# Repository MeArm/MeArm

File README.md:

MeArm - Pocket Sized Robot Arm 
===========================

The MeArm is a small robot arm, designed make robotics and coding available at low cost. The project has been hugely successful in its objectives, due to the massive number of clones that have been made and sold across the world. There isn't an online market place where you can't buy a copy of this project. We continue to support the product through income made from the sale of high quality robot kits, manufactured and shipped from the UK.

[MeArm Website](https://www.mearm.com/) Where kits are available to purchase.

[MeArm GitHub](https://github.com/MeArm) Code and resources.

[phenoptix Thingiverse](https://www.thingiverse.com/phenoptix/designs) Physical designs and dxf files, alternative hosting, and other designed products.

Controllers and firmware for the MeArm are available for many different platforms, and can all be found in our [company github](https://github.com/MeArm).

## Available Controllers

Arduino
  - [Library with Inverse Kinematics](https://github.com/MeArm/MeArm-Arduino)
  - pcb V1.0 - AKA Brains Board using Pro Mini Clone
  - pcb V2.0 - AKA MeArm Wifi using ESP8266

Raspberry Pi
  - [node.js control](https://github.com/MeArm/mearm-js)
  - pcb V1.0 MeArm Pi

micro:bit 
  - [pxt adds blocks to makecode](https://github.com/MeArm/pxt-microbit-mearm)
  - [makecode hosted on microbit.org](https://makecode.microbit.org/22476-86653-83739-82174)
  - pcb all versions AKA MeArm micro:bit 

BeagleBoneBlack -[ Software hosted by Bob Stone](https://github.com/RorschachUK/meArmBBB)

Espruino - [JS Hardware with MeArm Examples](https://www.espruino.com/MeArm)

SparkCore - [Software with features such as S-Curve movements
](https://github.com/Hack-a-Day/Spark-MeArm)

Repository Contents
-------------------
This repository contains the design and cutting files for the MeArm. The MeArm is an Open Source 4DOF robot arm. It is intended to be a low cost and accessible robotics project for STEAM education.

Laser cut (3mm) dxf files and Assembly instruction pdf files are sorted into folders based on versions.

Files are collected from the various sources listed above.

## Watch the Build Video on YouTube

Version History
---------------

Available in this repository

* V3.0 Revised with no elastic bands, still requires a PCB. Build time around 40 minutes.
* V2.0 Designed for MeArm Pi Kickstarter, incorporates a PCB in the base. Requires elastic bands or nitrile O rings. Build time 30 minutes.
* V1.0 First finished version. No PCB required. Build time around 2 hours.

All hosted on Thingiverse .

* V1.0 ([First Finished Version](http://www.thingiverse.com/thing:993759))
* V0.4 ([Considered the Beta Arm](http://www.thingiverse.com/thing:360108))
* V0.3 ([Considered the Alpha Arm](http://www.thingiverse.com/thing:298820))
* V0.2 ([Heavy Weight Revision](http://www.thingiverse.com/thing:293707))
* V0.1 ([Proof of Concept](http://www.thingiverse.com/thing:257990))

License Information
-------------------
The hardware is released under [Creative Commons Share-alike 3.0](http://creativecommons.org/licenses/by-sa/3.0/).  
All other code is open source so please feel free to do anything you want with it; you buy me a beer if you use this and we meet someday ([Beerware license](http://en.wikipedia.org/wiki/Beerware)).
Also this boiler plate is yoinked from Sparkfun with thanks. Images are CC-SA-NC soz, have the files and design but take your own pics ;)

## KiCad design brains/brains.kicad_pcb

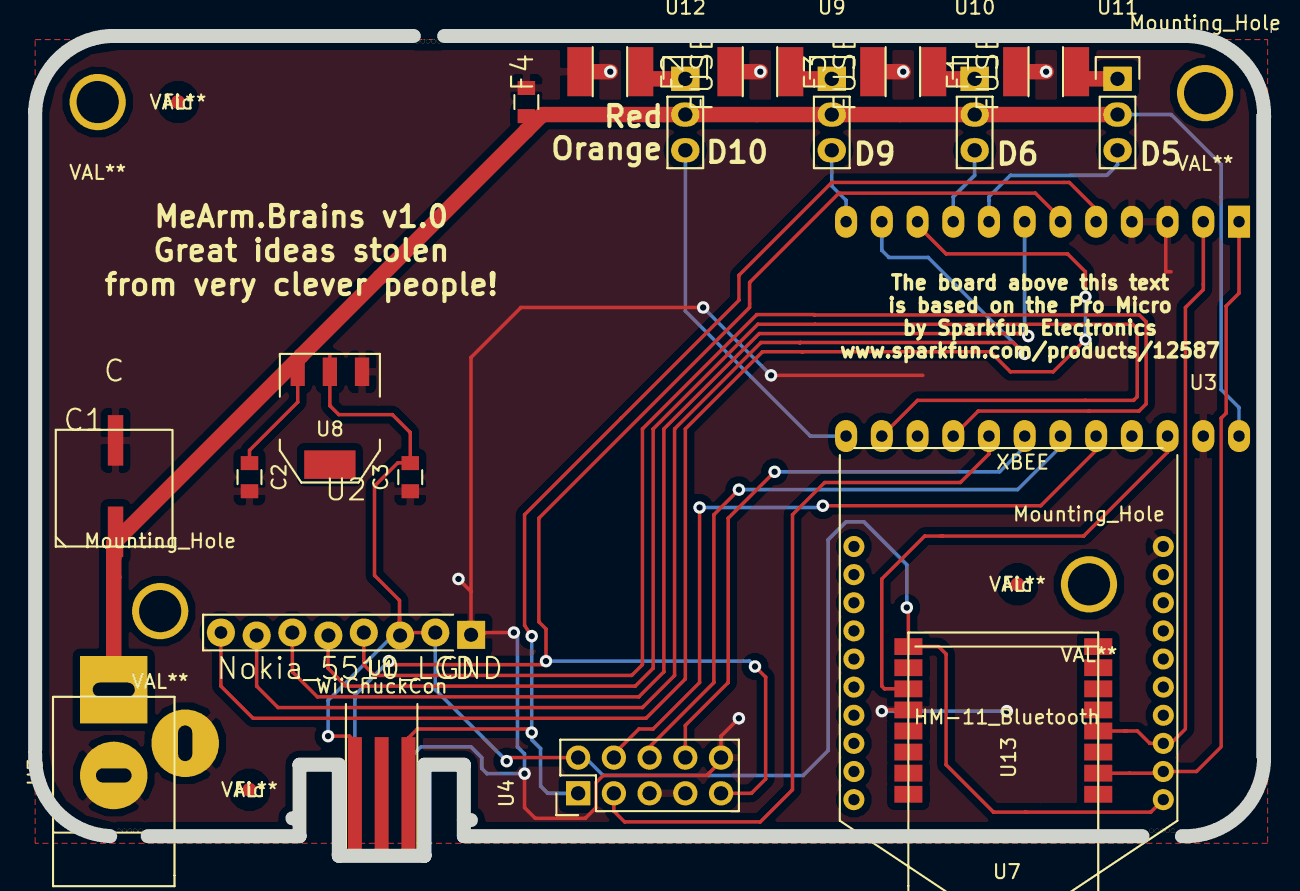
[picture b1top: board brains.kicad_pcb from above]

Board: 4 copper layers, 87.4 x 58.4 mm, 26 parts (0 on the bottom side), 25 nets.

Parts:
C1: C; EEE1CA471UP_Capacitor
C2: 10uF; C_0805
C3: 22uF; C_0805
C4: C; C_0805
F1, F2, F3, F4: FUSE; Surface_Mount_1812_Polyfuse
Fid: VAL**; Fid
Fid#2, Fid#3: VAL**; Fid
Mounting_Hole: VAL**; Mounting_Hole
Mounting_Hole#2, Mounting_Hole#3: VAL**; Mounting_Hole
U1: WiiChuckCon; WiiChuck
U2: Nokia_5510_LCD; Nokia5510LCD
U3: promicro; DIP-24__600_ELL
U4: JoyConnectISP; Pin_Header_Straight_2x05
U5: JACK_2MM1; JACK_ALIM
U7: HM-11_Bluetooth; HM-11_BT
U8: AP1117_V_REG; SOT-223
U9, U10, U11, U12: Pin_Header_Straight_1x03
U13: XBEE

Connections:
+3V3: C3.2, U1.1, U2.6, U2.7, U4.2, U7.9, U8.2, U13.1
+6V: C1.1, C2.1, C4.1, U3.24, U5.1, U8.3, U9.2, U10.2, U11.2, U12.2
A0: U3.17, U4.3
A1: U3.18, U4.8
A2: U3.19, U4.6
A3: U3.20, U4.4
BT_RX: U3.2, U7.4, U13.3
BT_TX: U3.1, U7.2, U13.2
CLAW: U3.13, U12.3
GND: C1.2, C2.2, C3.1, C4.2, F1.2, F2.2, F3.2, F4.2, U1.6, U2.8, U3.3, U3.4, U3.23, U4.5, U4.7, U4.10, U5.2, U5.3, U7.12, U8.1, U13.10
I2C_SCLK: U1.4, U3.6, U4.9
I2C_SDA: U1.3, U3.5, U4.1
LCD_CE: U2.2, U3.11
LCD_DC: U2.3, U3.7
LCD_RST: U2.1, U3.10
LEFT: U3.9, U10.3
MOSI_D16: U2.4, U3.14
unnamed: F1.1, U9.1
unnamed: F2.1, U10.1
unnamed: F3.1, U11.1
unnamed: F4.1, U12.1
RIGHT: U3.8, U11.3
RST: U3.22, U7.11
SCLK_D15: U2.5, U3.16
WAIST: U3.12, U9.3

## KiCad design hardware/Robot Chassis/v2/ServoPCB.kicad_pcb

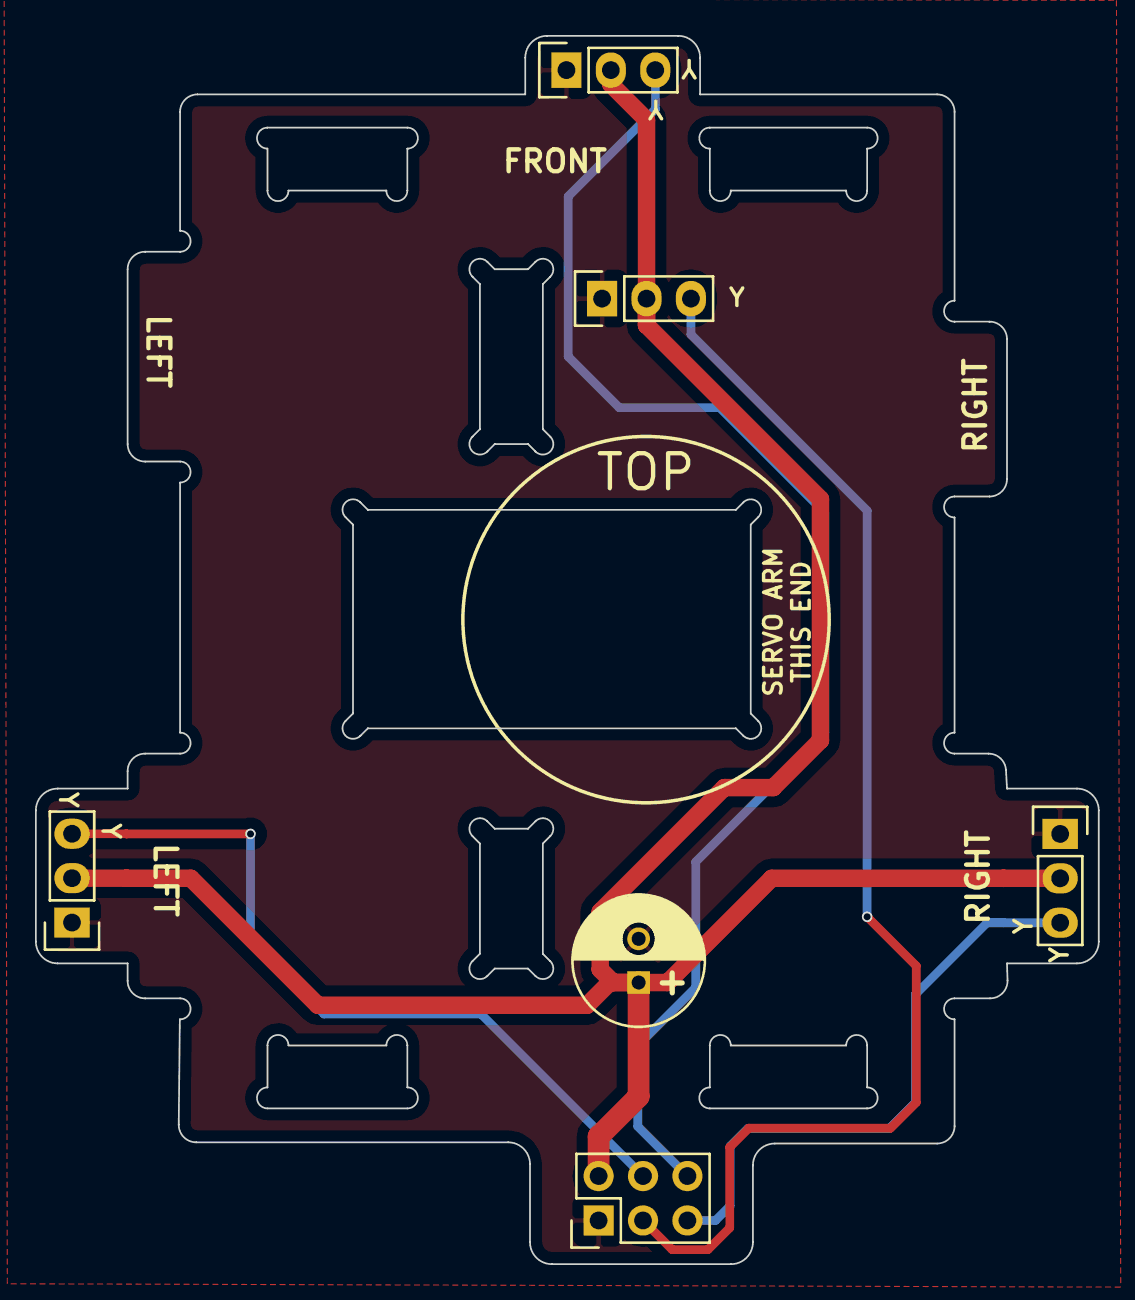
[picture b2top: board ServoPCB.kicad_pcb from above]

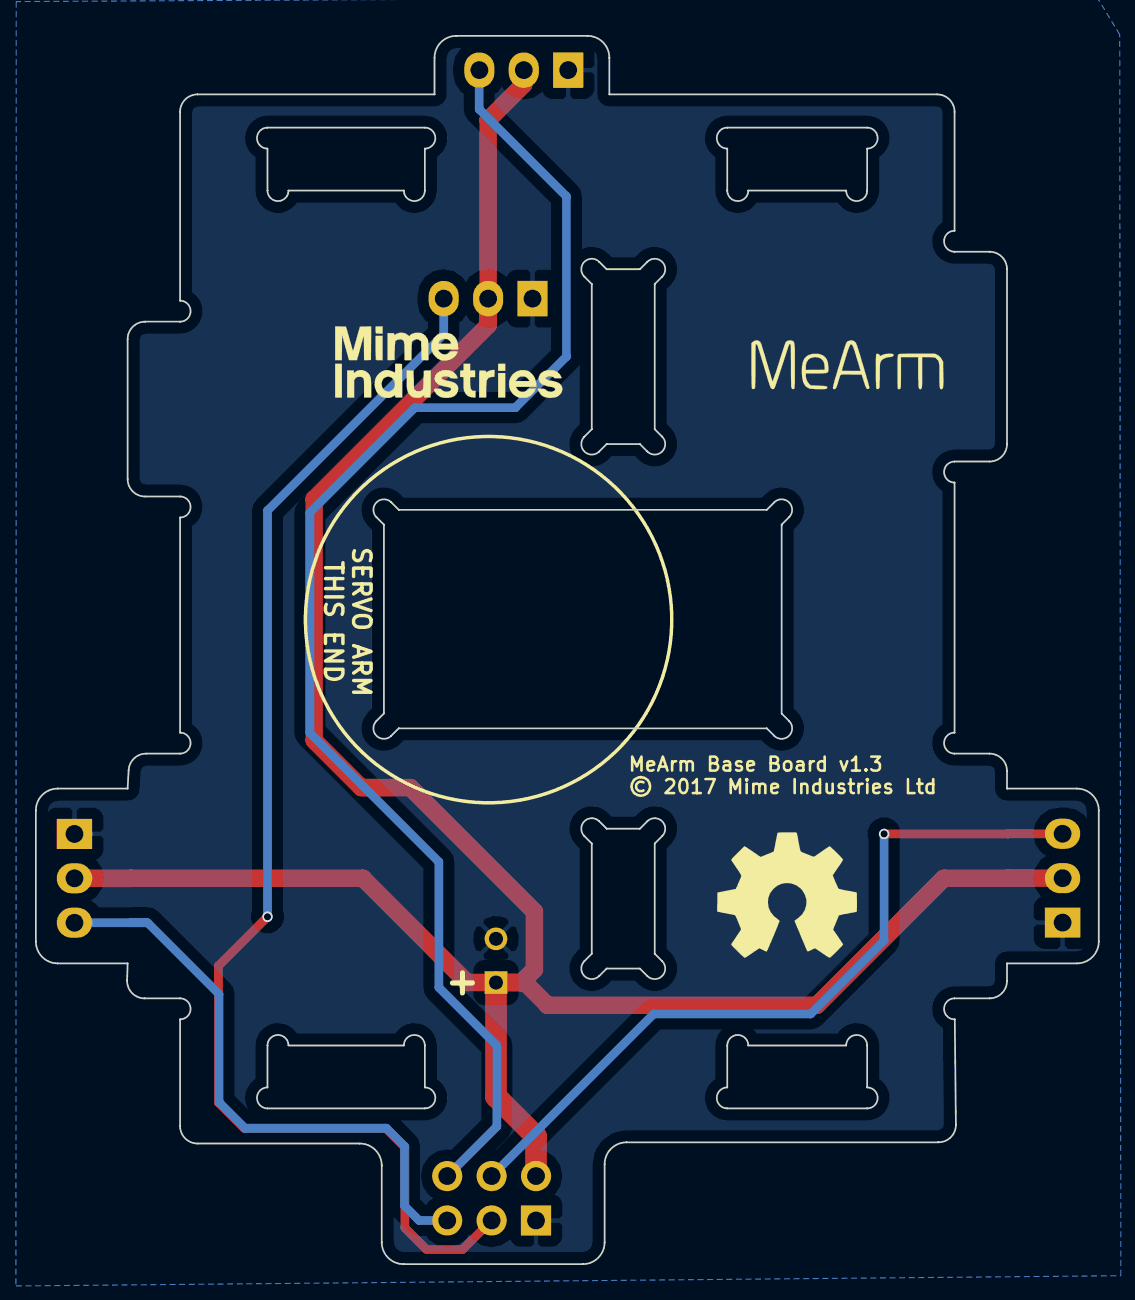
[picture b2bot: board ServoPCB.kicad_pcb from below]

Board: 2 copper layers, 60.8 x 70.3 mm, 9 parts (3 on the bottom side), 6 nets.

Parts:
ART1: OSHW-LOGO; OSHW_LOGO
ART2: LOGO; MIME_LOGO
ART3: LOGO; MEARM_LOGO_NEW
C1: 470uF; C_Radial_D7.5_L11.2_P2.5
P1: CONNECTOR; Pin_Header_Straight_2x03
P2, P3, P4, P5: Pin_Header_Straight_1x03

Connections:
GND: C1.2, P1.1, P2.1, P3.1, P4.1, P5.1
unnamed: P1.3, P2.3
unnamed: P1.4, P3.3
unnamed: P1.5, P4.3
unnamed: P1.6, P5.3
VCC: C1.1, P1.2, P2.2, P3.2, P4.2, P5.2

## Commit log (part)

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2014-04-23 Arduino Code for MeArm
    Control with 10k Pots
2014-05-01 Typo in pin numbering comments
2014-05-07 Inverse Kinematics in the XZ plane
    Should be trivial to add it to the XY too. Still uses 10k pots for
    input. Out of time for today.
2014-05-07 Readme Added
2014-05-07 Commented and cleaned up
    Functionality much the same but cleaned up a little and commented so at
    least I can understand it come tomorrow.
2014-05-08 Y to Z
2014-05-11 More documentation
2014-05-13 Wii Classic IK sketch added
2014-05-13 add isReachable()
2014-12-13 Animate MeArm
2014-12-17 First Commit
    Upload of KiCAD MeArm Controller Leonardo Files
2015-03-26 New Board Version
    Retired the previous MeBrain board for this Brains board. v2.0 all files
    available for your delectation.
2015-03-26 Updated folder names on README
2015-09-01 V1.0 Update
    Kickstarter Production version
2016-02-26 pdf schematic as requested
2016-04-13 Pro Micro Image File
2016-11-29 Moving Old Project Files
2016-11-29 Add Code Folder to MeArm
    Getting together MeArm Resources and pull code folder from old MeArm
    Github Organisation.
2016-11-29 more moving
2016-11-29 Add Hardware Folder to MeArm Structure
    Hardware folder to contain all hardware related files, PCB and
    structure.
2016-11-29 Moved Arduino Files to Arduino Folder
2016-11-29 Added Deluxe Kit Default Code and Rearrange Files
2016-11-29 Fixed Readme
2016-11-29 Fixed README (again)
2016-11-29 Links to code for BBB, Raspberry Pi and Spark Core
2016-11-29 Fixed readme again (hopefully)
2017-03-09 Re-worked to bring in the dxf files, starting with v0.1
2017-03-09 Adding v0.2
2017-03-09 Adding v0.3
2017-03-09 Adding v0.4
2017-03-09 Adding v1.0
2017-03-09 Update README to point to v2
2017-03-09 Bringing in the version of the MeArm used for demoing in the Kickstarter
2017-03-14 Add v1.1 of the MeArm design
2022-10-05 v1 to v3 files collected together
2023-03-03 Detail and essentials
    Filled out readme a little more and added KiCad files for the PCB. Would gerbers be more useful? If anyone is looking and cares please let me know.

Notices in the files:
brains/brains.kicad_pcb:
CC-BY-SA 3.0
hardware/Robot Chassis/v2/ServoPCB.kicad_pcb:
© 2017 Mime Industries Ltd
